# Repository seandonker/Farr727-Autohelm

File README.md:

<b>Project Update<br>
   --------------
Because of different factors such as school, work, and living location, our Farr Sailboat will likely not see water for a few years. For this reason, the project has been halted as on-boat testing is needed for any further programming.

# Farr727-Autohelm

Tiller push/pull based autohelm for a sailboat. Project includes C++ code, CAD files, circuit board files, and pictures. 
This design was started in June, 2021 and it is almost complete, just requiring a few more 3D printed parts, the GUI design to be finished,
and final PID tuning on the boat. 

Commercial auto helms are available for boats using a tiller instead of a wheel (wheel or rudder moving auto helms are much more common) but they are expensive
for the quality of product you get. They are often loud, have primitive controls, and require a separate power source on the boat (which our boat does not have).
The goal of this project was to create an autohelm that was fully battery operated, had a better user interface experience, and was very quiet in operation. 

This project features two main design elements; the controller and the tiller arm receiver. The controller's main function is to sense the boat's
heading and send that data to the tiller arm receiver where it will be translated into rudder movement to correct for any deviations in the boat's course. 
The receiver takes the data sent by the controller and uses a PID loop to determine the correct amount of stepper motor rotation which translates into how
far the tiller moves left or right. A simple diagram of the system can be seen below.  

<b>CONTROLLER<br>
   ----------
The controller unit features a relatively powerful arm microcontroller (Teensy 4.0) that runs a 9-axis IMU heading routine. The teensy also communicates with the bluetooth radio (nrf2401+) in order to send the error in the heading, PID values, and tilt angle of the boat to the receiver. The controller also features four momentary buttons for user input along with an e-paper display and a real time clock as the pesky lift bridge in port stanley only opens every 30 minutes! It uses a wireless charging coil for charging in order to keep it as water tight as possible and the two internal 18650 batteries should last 8+ hours.

<b>TILLER ARM RECEIVER<br>
   -------------------
The tiller arm receiver has a more power efficient and slower microcontroller (Teensy LC) as its main function is to receive the PID data, run the PID loop, and create the desired pulses for the stepper motor driver and none of those routines require much processing. The trinamic 2209 stepper motor driver was used because of its patented quiet step function so the motor operates almost silently. To power the unit, 12 18650 batteries were used in a 6s2p configuration to provide a maximum of 25.2 volts for the motor driver. This high voltage allows the motor to spin faster as the high voltage overcomes the back EMF reducing the risk of stalling and stuttering. The microcontroller monitors the voltage of the battery pack through a voltage divider and periodically sends back the value to be displayed on the control unit. 

<b>FINISHING TOUCHES<br>
   -----------------
Before the system can be tested, the GUI has to be roughly completed in order to change PID values on the fly. As for 3D printed parts, a mounting bracket where the controller can slide into needs to be designed. After testing the system and tuning of the motor current on the motor driver, a cover for the tiller arm will be designed and printed as well. The final step will likely be making the GUI look more professional with graphics and better element alignment.

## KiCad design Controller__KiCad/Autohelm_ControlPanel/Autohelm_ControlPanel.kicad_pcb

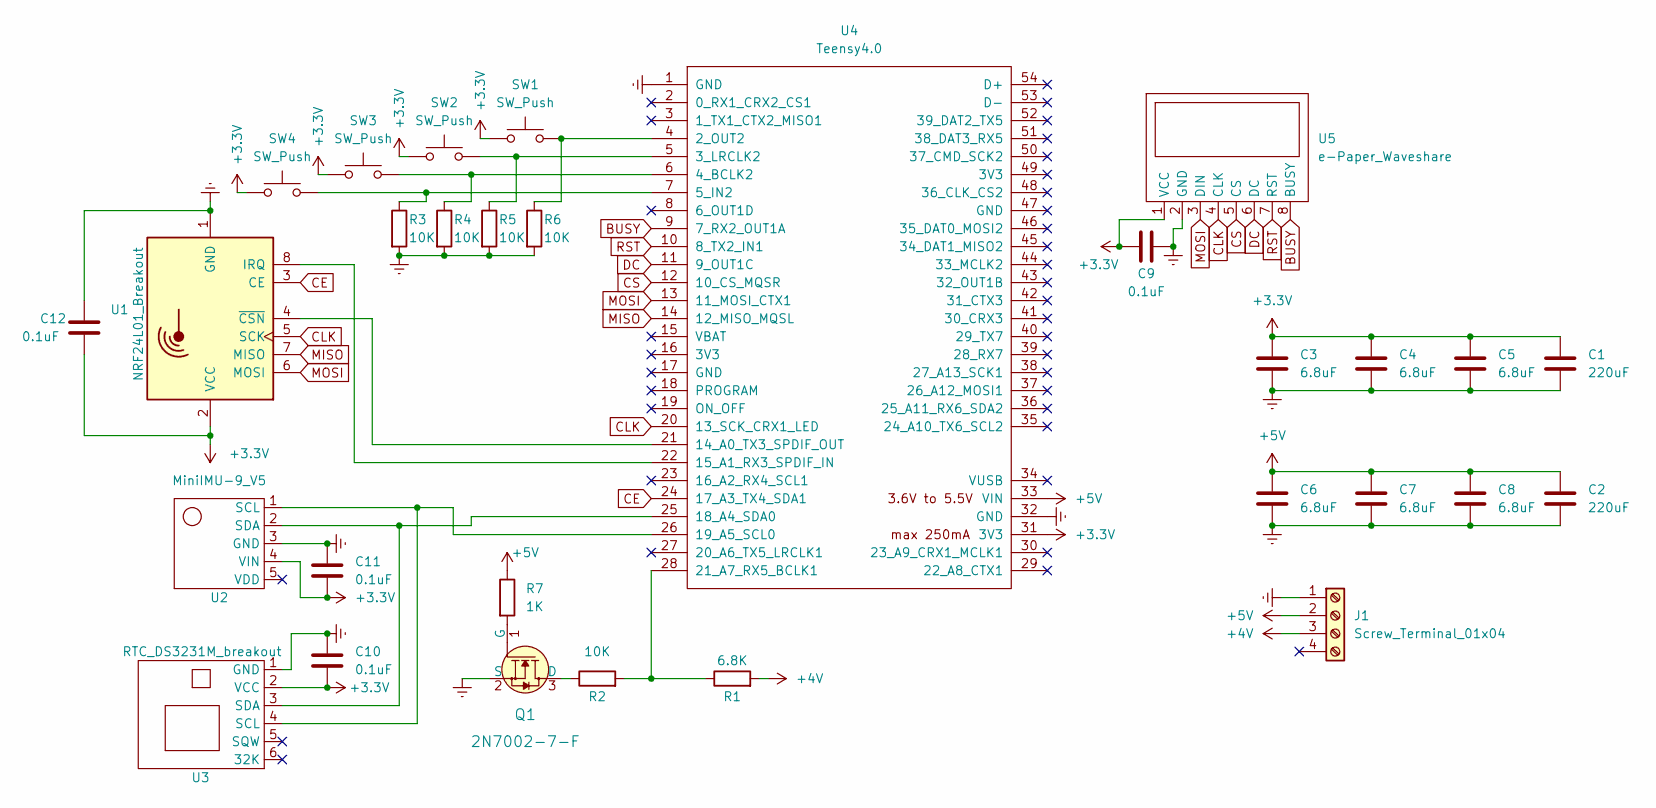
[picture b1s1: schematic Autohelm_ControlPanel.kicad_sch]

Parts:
C1, C2: 220uF; CP_Radial_D5.0mm_P2.00mm
C3, C4, C5, C6, C7, C8: 6.8uF; C_1812_4532Metric
C9, C10, C11, C12: 0.1uF; C_1812_4532Metric
J1: Screw_Terminal_01x04; TerminalBlock_bornier-4_P5.08mm
Q1: 2N7002-7-F; SOT-23-3; MPN 2N7002-7-F; Digi-Key_PN 2N7002-FDICT-ND
R1: 6.8K; R_0805_2012Metric
R2, R3, R4, R5, R6: 10K; R_0805_2012Metric
R7: 1K; R_0805_2012Metric
SW1, SW2, SW3, SW4: SW_Push; TerminalBlock_bornier-2_P5.08mm
U1: NRF24L01_Breakout; nRF24L01_Breakout
U2: MiniIMU-9_V5; PinHeader_1x04_P2.54mm_Vertical
U3: RTC_DS3231M_breakout; PinHeader_1x04_P2.54mm_Vertical
U4: Teensy4.0; Teensy40
U5: e-Paper_Waveshare; PinHeader_1x08_P2.54mm_Vertical

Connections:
+3.3V: C1.1, C3.1, C4.1, C5.1, C9.2, C10.2, C11.2, C12.2, SW1.1, SW2.1, SW3.1, SW4.1, U1.2 (VCC), U2.4 (VIN), U3.2 (VCC), U4.31 (3V3), U5.1 (VCC)
+4V: J1.3, R1.2
+5V: C2.1, C6.1, C7.1, C8.1, J1.2, R7.1, U4.33 (VIN)
BUSY: U4.9 (7_RX2_OUT1A), U5.8 (BUSY)
CE: U1.3 (CE), U4.24 (17_A3_TX4_SDA1)
CLK: U1.5 (SCK), U4.20 (13_SCK_CRX1_LED), U5.4 (CLK)
CS: U4.12 (10_CS_MQSR), U5.5 (CS)
DC: U4.11 (9_OUT1C), U5.6 (DC)
Earth: C1.2, C2.2, C3.2, C4.2, C5.2, C6.2, C7.2, C8.2, C9.1, C10.1, C11.1, C12.1, J1.1, Q1.2 (S), R3.2, R4.2, R5.2, R6.2, U1.1 (GND), U2.3 (GND), U3.1 (GND), U4.1 (GND), U4.32 (GND), U5.2 (GND)
MISO: U1.7 (MISO), U4.14 (12_MISO_MQSL)
MOSI: U1.6 (MOSI), U4.13 (11_MOSI_CTX1), U5.3 (DIN)
unnamed: Q1.1 (G), R7.2
unnamed: Q1.3 (D), R2.1
unnamed: R1.1, R2.2, U4.28 (21_A7_RX5_BCLK1)
unnamed: R3.1, SW4.2, U4.7 (5_IN2)
unnamed: R4.1, SW3.2, U4.6 (4_BCLK2)
unnamed: R5.1, SW2.2, U4.5 (3_LRCLK2)
unnamed: R6.1, SW1.2, U4.4 (2_OUT2)
unnamed: U1.4 (~CSN), U4.21 (14_A0_TX3_SPDIF_OUT)
unnamed: U1.8 (IRQ), U4.22 (15_A1_RX3_SPDIF_IN)
unnamed: U2.1 (SCL), U3.4 (SCL), U4.26 (19_A5_SCL0)
unnamed: U2.2 (SDA), U3.3 (SDA), U4.25 (18_A4_SDA0)
RST: U4.10 (8_TX2_IN1), U5.7 (RST)

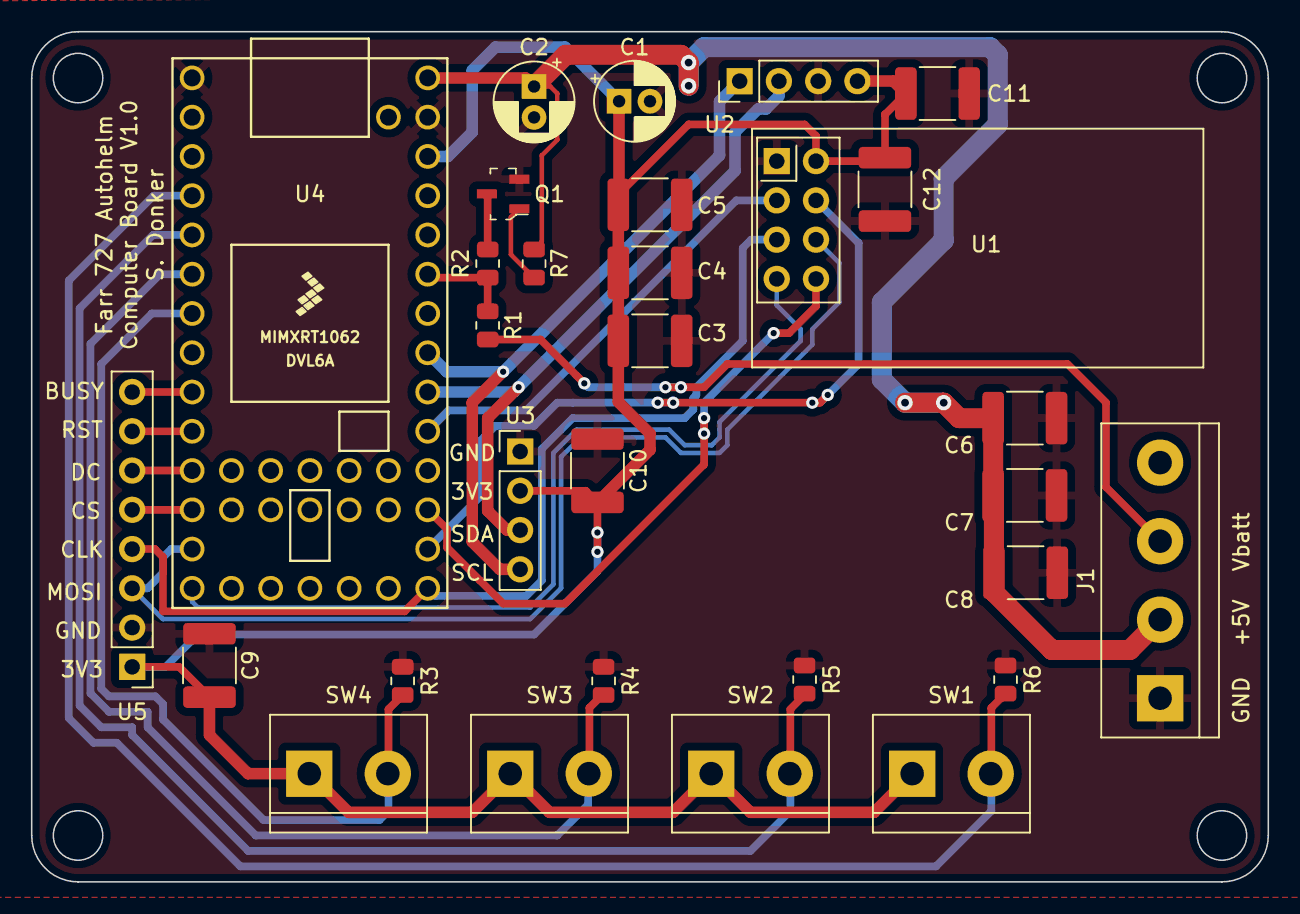
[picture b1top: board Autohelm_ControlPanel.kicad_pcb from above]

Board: 2 copper layers, 80.0 x 55.0 mm, 30 parts (0 on the bottom side), 23 nets.

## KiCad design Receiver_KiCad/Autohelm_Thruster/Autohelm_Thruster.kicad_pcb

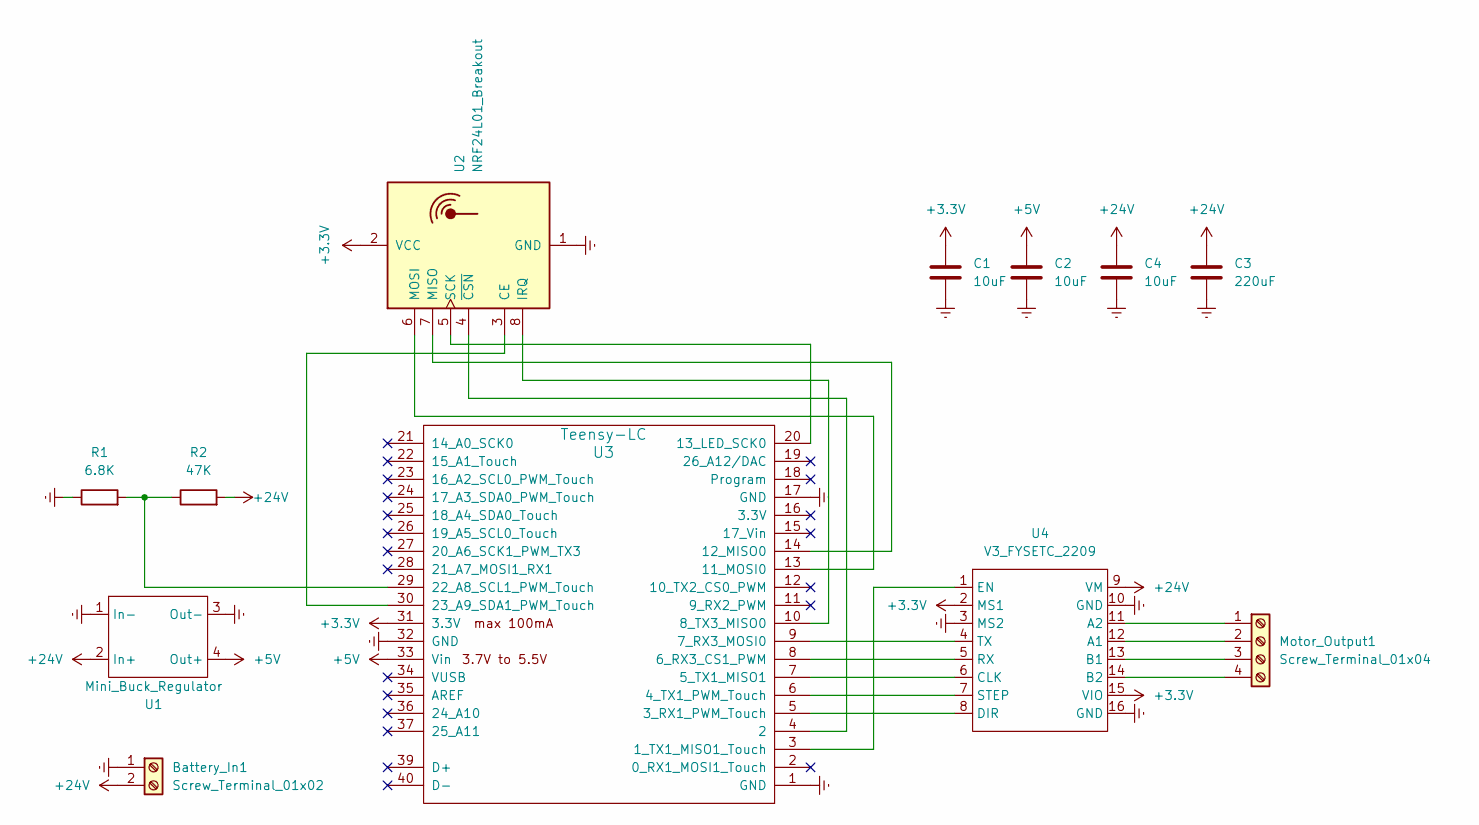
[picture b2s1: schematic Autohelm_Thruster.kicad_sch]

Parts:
Battery_In1: Screw_Terminal_01x02; TerminalBlock_bornier-2_P5.08mm
C1, C2, C4: 10uF; C_1812_4532Metric
C3: 220uF; CP_Radial_D10.0mm_P5.00mm
Motor_Output1: Screw_Terminal_01x04; TerminalBlock_bornier-4_P5.08mm
R1: 6.8K; R_0805_2012Metric
R2: 47K; R_0805_2012Metric
U1: Mini_Buck_Regulator; Mini_360_Buck_Convertor_SMD
U2: NRF24L01_Breakout; nRF24L01_Breakout
U3: Teensy-LC; Teensy_LC
U4: V3_FYSETC_2209; TMC2209_breakout

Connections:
+3.3V: C1.1, U2.2 (VCC), U3.31 (3.3V), U4.2 (MS1), U4.15 (VIO)
+5V: C2.1, U1.4 (Out+), U3.33 (Vin)
+24V: Battery_In1.2, C3.1, C4.1, R2.2, U1.2 (In+), U4.9 (VM)
Earth: Battery_In1.1, C1.2, C2.2, C3.2, C4.2, R1.1, U1.1 (In-), U1.3 (Out-), U2.1 (GND), U3.1 (GND), U3.17 (GND), U3.32 (GND), U4.3 (MS2), U4.10 (GND), U4.16 (GND)
unnamed 4: Motor_Output1.1, U4.11 (A2); also elsewhere on the board
unnamed 5: Motor_Output1.2, U4.12 (A1); also elsewhere on the board
unnamed 6: Motor_Output1.3, U4.13 (B1); also elsewhere on the board
unnamed 7: Motor_Output1.4, U4.14 (B2); also elsewhere on the board
unnamed: R1.2, R2.1, U3.29 (22_A8_SCL1_PWM_Touch)
unnamed: U2.3 (CE), U3.30 (23_A9_SDA1_PWM_Touch)
unnamed: U2.4 (~CSN), U3.4 (2)
unnamed: U2.5 (SCK), U3.20 (13_LED_SCK0)
unnamed: U2.6 (MOSI), U3.13 (11_MOSI0)
unnamed: U2.7 (MISO), U3.14 (12_MISO0)
unnamed: U2.8 (IRQ), U3.10 (8_TX3_MISO0)
unnamed: U3.3 (1_TX1_MISO1_Touch), U4.1 (EN)
unnamed: U3.5 (3_RX1_PWM_Touch), U4.8 (DIR)
unnamed: U3.6 (4_TX1_PWM_Touch), U4.7 (STEP)
unnamed: U3.7 (5_TX1_MISO1), U4.6 (CLK)
unnamed: U3.8 (6_RX3_CS1_PWM), U4.5 (RX)
unnamed: U3.9 (7_RX3_MOSI0), U4.4 (TX)

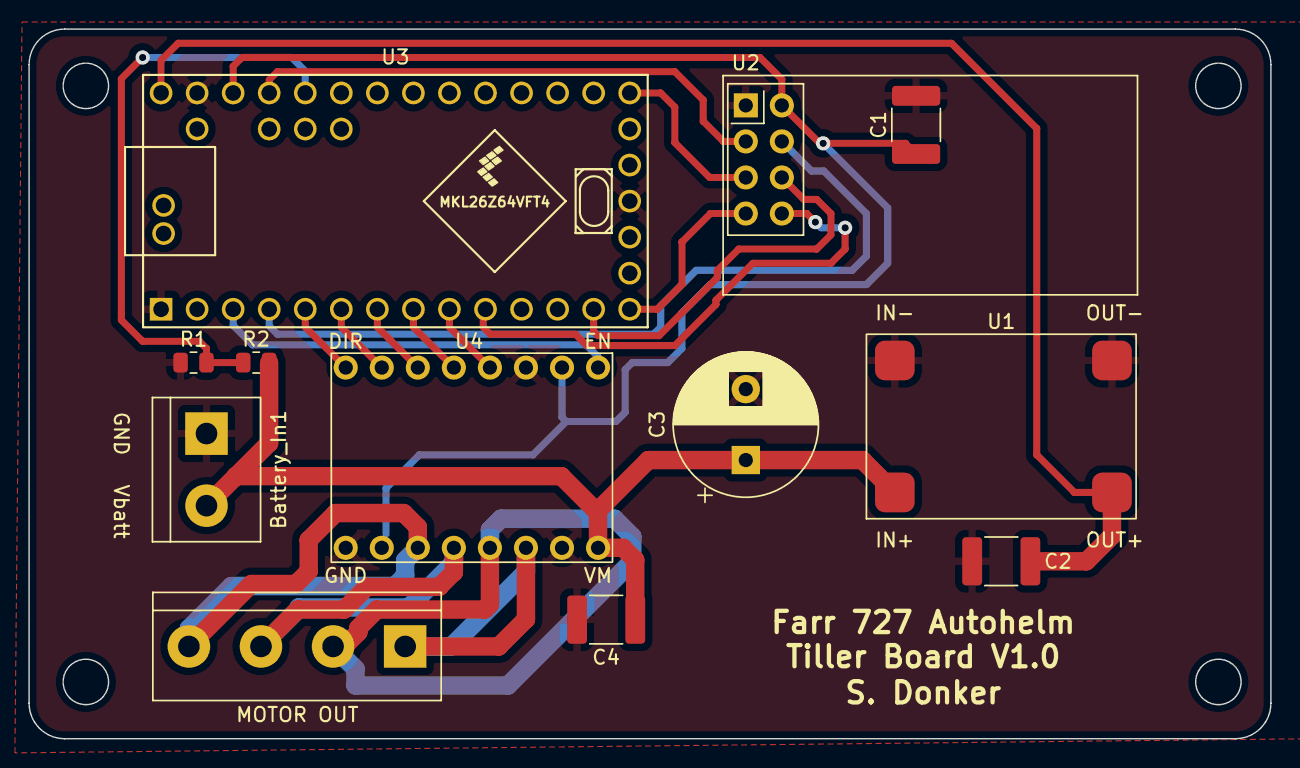
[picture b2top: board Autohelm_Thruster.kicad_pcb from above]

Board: 2 copper layers, 87.5 x 50.0 mm, 12 parts (0 on the bottom side), 21 nets.

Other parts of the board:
MOTOR OUT: Screw_Terminal_01x04; TerminalBlock_bornier-4_P5.08mm

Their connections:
unnamed 4: MOTOR OUT.1; also elsewhere on the board
unnamed 5: MOTOR OUT.2; also elsewhere on the board
unnamed 6: MOTOR OUT.3; also elsewhere on the board
unnamed 7: MOTOR OUT.4; also elsewhere on the board

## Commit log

2023-01-03 Code for main control unit (Compass, Display, Buttons)
2023-01-03 Code for tiller driver (stepper motor)
2023-01-03 CAD for circuit board (includes GERBER output)
2023-01-05 try picture
2023-01-06 Added images and descriptions.
2023-01-06 Fixed picture size
2023-01-23 Spelling
2023-03-03 Added baot picture
2023-03-27 Added underlines
